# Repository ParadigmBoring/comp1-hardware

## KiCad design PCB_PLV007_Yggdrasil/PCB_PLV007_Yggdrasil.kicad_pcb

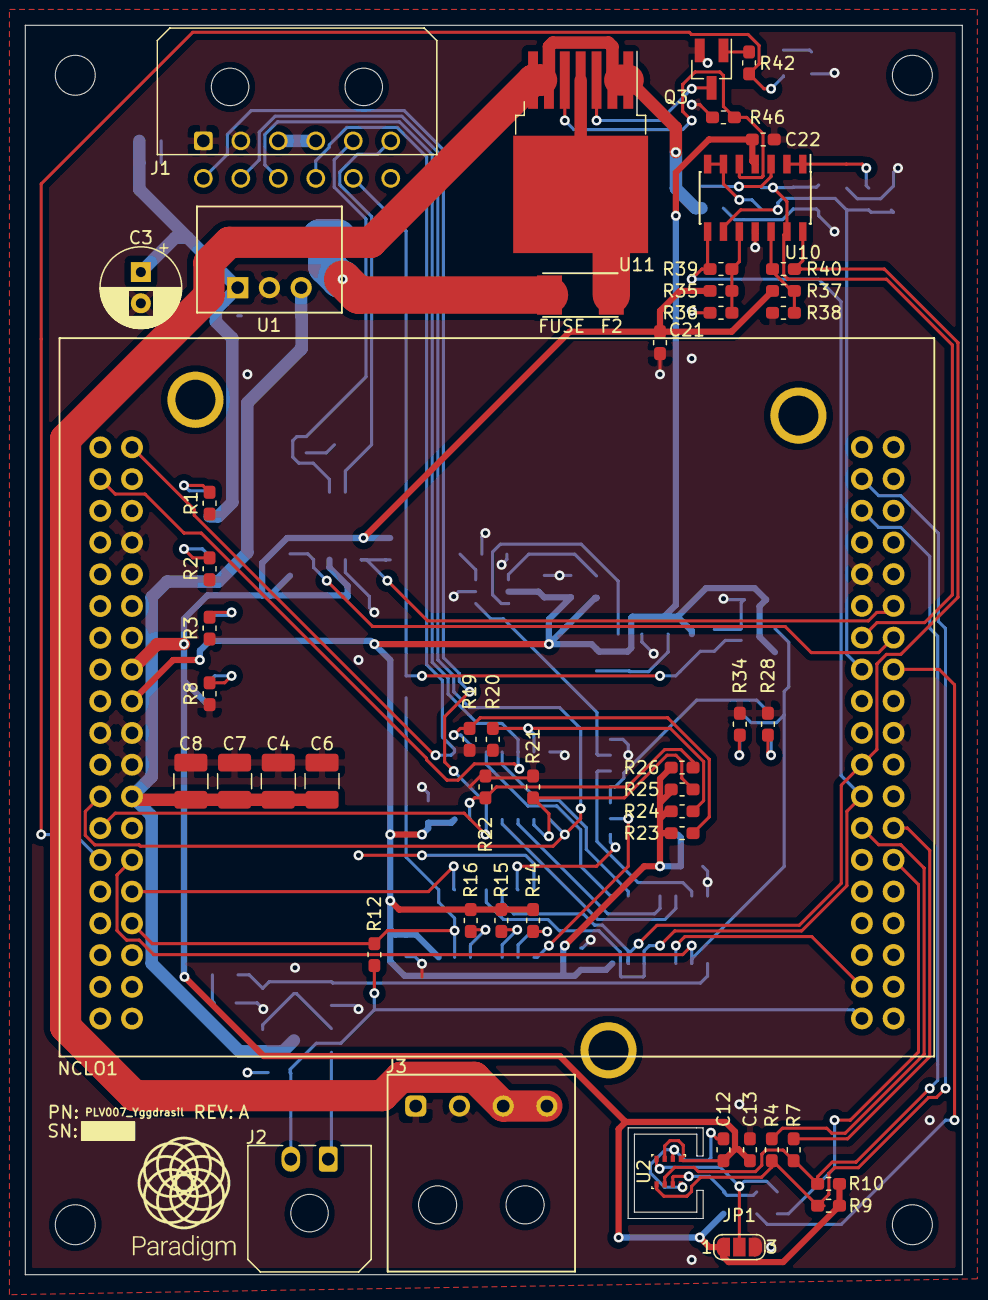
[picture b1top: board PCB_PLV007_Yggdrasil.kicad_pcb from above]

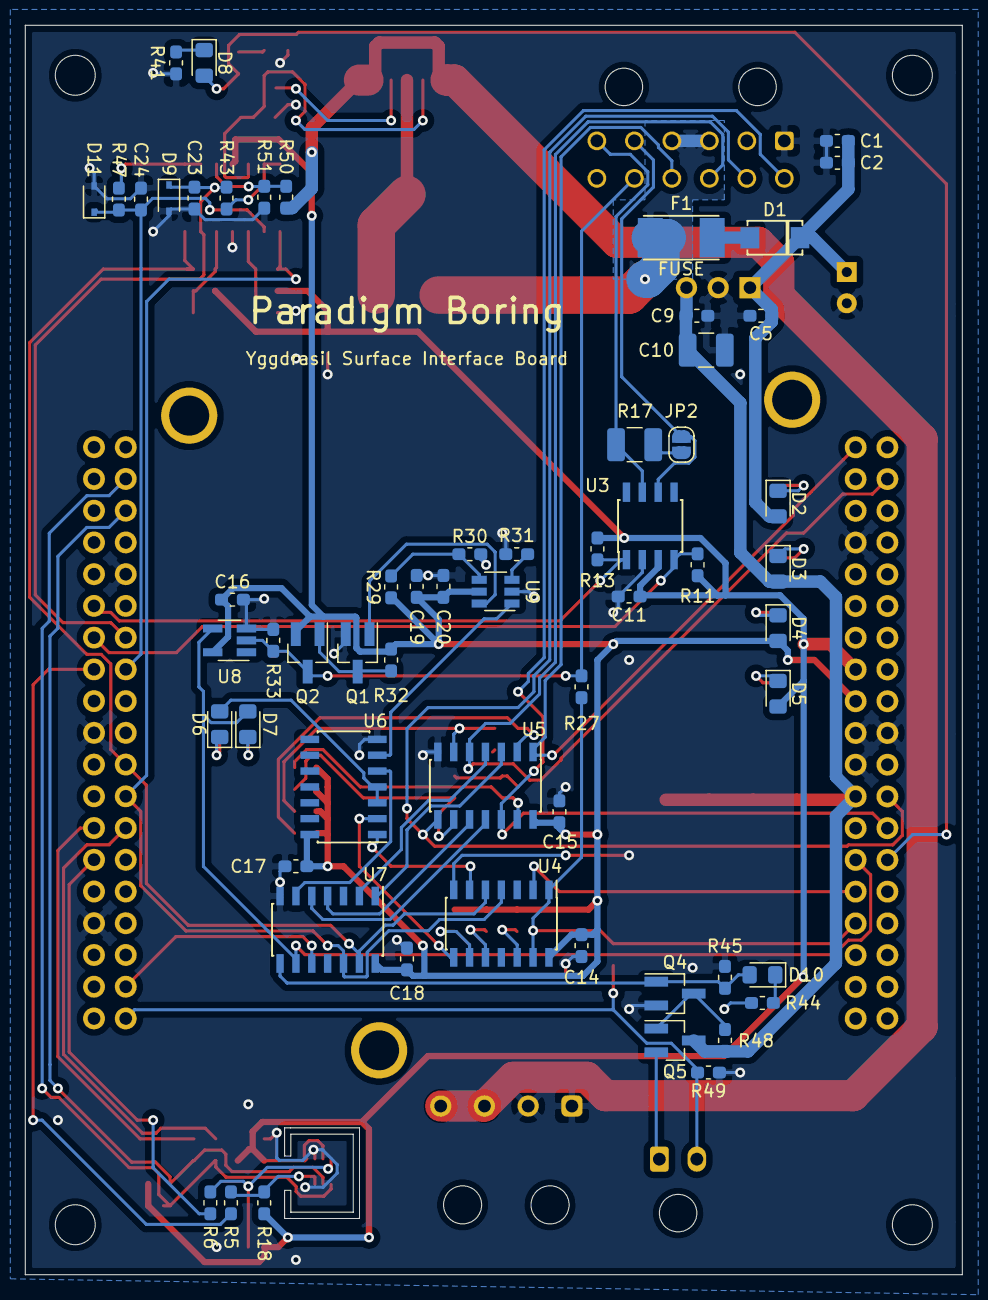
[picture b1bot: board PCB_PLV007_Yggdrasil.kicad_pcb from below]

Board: 2 copper layers, 75.0 x 100.0 mm, 110 parts (60 on the bottom side), 76 nets.

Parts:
C1, C2: DNP; C_0603_1608Metric_Pad1.05x0.95mm_HandSolder
C3: 47uF; CP_Radial_D6.3mm_P2.50mm
C4, C6, C7, C8, C10: 10uF; C_1210_3225Metric_Pad1.42x2.65mm_HandSolder
C5, C13, C20: 1uF; C_0603_1608Metric_Pad1.05x0.95mm_HandSolder
C9, C11, C12, C14, C15, C16, C17, C18, C19, C21, C22: 0.1uF; C_0603_1608Metric_Pad1.05x0.95mm_HandSolder
C23, C24: 0.47uF; C_0603_1608Metric_Pad1.05x0.95mm_HandSolder
D1: D_Schottky; DO-221AC
D2: 28V; LED_0805_2012Metric_Pad1.15x1.40mm_HandSolder
D3: 12V; LED_0805_2012Metric_Pad1.15x1.40mm_HandSolder
D4: 5V; LED_0805_2012Metric_Pad1.15x1.40mm_HandSolder
D5: 3V3; LED_0805_2012Metric_Pad1.15x1.40mm_HandSolder
D6: QB_IN; LED_0805_2012Metric_Pad1.15x1.40mm_HandSolder
D7: QB_OUT; LED_0805_2012Metric_Pad1.15x1.40mm_HandSolder
D8, D10: LED; LED_0805_2012Metric_Pad1.15x1.40mm_HandSolder
D9, D11: 3.3V; D_SOD-323
F1: 2A; BelFuse_0679H
F2: 15A; BelFuse_0679H
J1: Conn_01x12; Molex_Micro-Fit_3.0_43045-1200_2x06_P3.00mm_Horizontal
J2: UMBILICAL_MASTER; Molex_Micro-Fit_3.0_43650-0200_1x02_P3.00mm_Horizontal
J3: UMBILICAL_POWER; Molex_Ultra-Fit_172310-1204_1x04
JP1: BME280_ADDR; SolderJumper-3_P1.3mm_Open_RoundedPad1.0x1.5mm_NumberLabels
JP2: CAN_TERM; SolderJumper-2_P1.3mm_Open_RoundedPad1.0x1.5mm
NCLO1: NUCLEO-L476RG; ST_Nucleo-64
Q1, Q4: DMG2302UK-7; SOT-23_Handsoldering
Q2, Q5: DMP2123L-7; SOT-23_Handsoldering
Q3: MMBTA06LT1G; SOT-23_Handsoldering
R1: 11K; R_0603_1608Metric_Pad1.05x0.95mm_HandSolder
R2, R9, R10: 4.7K; R_0603_1608Metric_Pad1.05x0.95mm_HandSolder
R3: 1.5K; R_0603_1608Metric_Pad1.05x0.95mm_HandSolder
R4, R7, R14, R15, R16: 0; R_0603_1608Metric_Pad1.05x0.95mm_HandSolder
R5, R6, R11, R13, R19, R20, R21, R22, R23, R24, R25, R26: DNP; R_0603_1608Metric_Pad1.05x0.95mm_HandSolder
R8: 47; R_0603_1608Metric_Pad1.05x0.95mm_HandSolder
R12, R35, R37, R49, R51: 10K; R_0603_1608Metric_Pad1.05x0.95mm_HandSolder
R17: 120; R_1210_3225Metric_Pad1.42x2.65mm_HandSolder
R18: 0; C_0603_1608Metric_Pad1.05x0.95mm_HandSolder
R27, R32, R33: 47K; R_0603_1608Metric_Pad1.05x0.95mm_HandSolder
R28, R34, R41, R42, R43, R44, R47: 1K; R_0603_1608Metric_Pad1.05x0.95mm_HandSolder
R29: 1M; R_0603_1608Metric_Pad1.05x0.95mm_HandSolder
R30: 280K; R_0603_1608Metric_Pad1.05x0.95mm_HandSolder
R31: 604K; R_0603_1608Metric_Pad1.05x0.95mm_HandSolder
R36: 43K; R_0603_1608Metric_Pad1.05x0.95mm_HandSolder
R38: 16K; R_0603_1608Metric_Pad1.05x0.95mm_HandSolder
R39: 261K; R_0603_1608Metric_Pad1.05x0.95mm_HandSolder
R40: 95.3K; R_0603_1608Metric_Pad1.05x0.95mm_HandSolder
R45, R48, R50: 100K; R_0603_1608Metric_Pad1.05x0.95mm_HandSolder
R46: 2.1K; R_0603_1608Metric_Pad1.05x0.95mm_HandSolder
U1: R-78C12-1.0; Recom_R-78C-1.0
U2: BME280; Bosch_LGA-8_2.5x2.5mm_P0.65mm_ClockwisePinNumbering
U3: SN65HVD232; SOIC-8_3.9x4.9mm_P1.27mm
U4, U7: 74HC21; SOIC-14_3.9x8.7mm_P1.27mm
U5: 74HC266; SOIC-14_3.9x8.7mm_P1.27mm
U6: 74HC08; SOIC-14_3.9x8.7mm_P1.27mm
U8: 74LVC1G17; SOT-23-5_HandSoldering
U9: LTC6993xS6-1; TSOT-23-6
U10: LM2902; SOIC-14_3.9x8.7mm_P1.27mm
U11: BTS50055-1TMA; TO-263-7_TabPin4

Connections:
+3V3: C11.1, C12.1, C13.1, C21.1, D5.2, JP1.1, NCLO1.16, R9.1, R10.1, R11.1, R13.1, R18.1, R35.1, R37.1, U2.6, U2.8, U3.3
+5V: C14.1, C15.1, C16.1, C17.1, C18.1, C19.1, C20.1, C22.1, D4.2, NCLO1.18, Q2.2, R14.2, R15.2, R16.2, R23.1, R24.1, R25.1, R26.1, R29.1, R32.1, U4.14, U5.14, U6.14, U7.14, U8.5, U9.5, U10.4
+12V: C4.1, C6.1, C7.1, C8.1, C9.1, C10.1, D3.2, NCLO1.24, Q5.3, R48.1, U1.3
+28V: C1.1, C2.1, C3.1, C5.1, D1.1, D2.2, U1.1
/AvionicsHeartbeatTemplate/HEARTBEAT_INPUT_5: R14.1, U4.9
/AvionicsHeartbeatTemplate/HEARTBEAT_INPUT_6: R15.1, U4.10
/AvionicsHeartbeatTemplate/HEARTBEAT_INPUT_7: R16.1, U4.12
/BME280_CSB: R5.1, R18.2, U2.2
/BME280_SDO: JP1.2, R6.1, U2.5
/CANH: J1.6, R17.2, U3.7
/CANL: J1.5, JP2.2, U3.6
/CAN_RX: NCLO1.52, R11.2, U3.4
/CAN_TX: NCLO1.50, R13.2, U3.1
/C_SAFE: NCLO1.59, R40.1, U4.5, U7.13, U10.14
/C_SENSE: C23.1, D9.1, NCLO1.51, R43.2, U10.13
/HEARTBEAT: J1.11, Q2.3, R27.2, R33.1, U8.2
/HEARTBEAT_ADDRESS_1: J1.7, NCLO1.25, U5.12
/HEARTBEAT_ADDRESS_2: J1.8, NCLO1.23, U5.8
/HEARTBEAT_ADDRESS_3: J1.9, NCLO1.3, U5.5
/HEARTBEAT_ADDRESS_4: J1.10, NCLO1.2, U5.1
/HEARTBEAT_BUFF: D7.2, NCLO1.28, U7.9, U8.4
/HEARTBEAT_RESTART: NCLO1.32, R12.1, R27.1, U4.1, U4.13
/I2C_SCL: NCLO1.41, R4.1, R9.2, U2.4
/I2C_SDA: NCLO1.43, R7.1, R10.2, U2.3
/LOAD_SWITCH: D8.2, NCLO1.27, R42.2
/MCU_QB_INPUT: NCLO1.30, U4.2
/MCU_UHB_INPUT: NCLO1.73, U7.10
/UHB: J2.2, NCLO1.75, R12.2, R49.1
/UHBLS/UHB_MASTER: D10.2, Q4.1, R45.2, U7.8
/UHBLS/UMBILICAL_V+: J3.3, J3.4, R50.1, U11.1, U11.2, U11.6, U11.7
/VIN: F1.2, F2.2, J1.3, J1.4
/V_SAFE: NCLO1.61, R39.1, U4.4, U7.12, U10.8
/V_SENSE: C24.1, D11.1, NCLO1.53, R47.2, U10.9
GND: C1.2, C2.2, C3.2, C4.2, C5.2, C6.2, C7.2, C8.2, C9.2, C10.2, C11.2, C12.2, C13.2, C14.2, C15.2, C16.2, C17.2, C18.2, C19.2, C20.2, C21.2, C22.2, C23.2, C24.2, D9.2, D11.2, J1.1, J1.2, J3.1, J3.2, JP1.3, NCLO1.8, NCLO1.19, NCLO1.20, NCLO1.22, NCLO1.47, NCLO1.58, NCLO1.70, Q1.2, Q3.2, Q4.2, R1.2, R2.2, R3.2, R8.2, R19.1, R20.1, R21.1, R22.1, R28.2, R30.2, R31.2, R33.2, R34.2, R36.2, R38.2, R41.2, R44.2, R45.1, R46.2, R49.2, R51.2, U1.2, U2.1, U2.7, U3.2, U4.7, U5.7, U6.7, U7.7, U8.3, U9.2, U10.11
unnamed: D1.2, F1.1
unnamed: D2.1, R1.1
unnamed: D3.1, R2.1
unnamed: D4.1, R3.1
unnamed: D5.1, R8.1
unnamed: D6.1, R28.1
unnamed: D6.2, U6.3, U6.4
unnamed: D7.1, R34.1
unnamed: D8.1, R41.1
unnamed: D10.1, R44.1
unnamed: F2.1, U11.4
unnamed: J2.1, Q5.2
unnamed: JP2.1, R17.1
unnamed: NCLO1.54, R5.2
unnamed: NCLO1.63, R4.2
unnamed: NCLO1.64, R7.2
unnamed: NCLO1.66, R6.2
unnamed: Q1.1, U9.6
unnamed: Q1.3, Q2.1, R32.2
unnamed: Q3.1, R42.1
unnamed: Q3.3, U11.3
unnamed: Q4.3, Q5.1, R48.2
unnamed: R19.2, R23.2, U5.2
unnamed: R20.2, R24.2, U5.6
unnamed: R21.2, R25.2, U5.9
unnamed: R22.2, R26.2, U5.13
unnamed: R29.2, R30.1, U9.4
unnamed: R31.1, U9.3
unnamed: R35.2, R36.1, R39.2, U10.10
unnamed: R37.2, R38.1, R40.2, U10.12
unnamed: R43.1, U10.6, U10.7
unnamed: R46.1, U10.5, U11.5
unnamed: R47.1, U10.1, U10.2
unnamed: R50.2, R51.1, U10.3
unnamed: U4.6, U6.1
unnamed: U4.8, U6.2
unnamed: U5.3, U7.1
unnamed: U5.4, U7.2
unnamed: U5.10, U7.4
unnamed: U5.11, U7.5
unnamed: U6.5, U7.6
unnamed: U6.6, U9.1

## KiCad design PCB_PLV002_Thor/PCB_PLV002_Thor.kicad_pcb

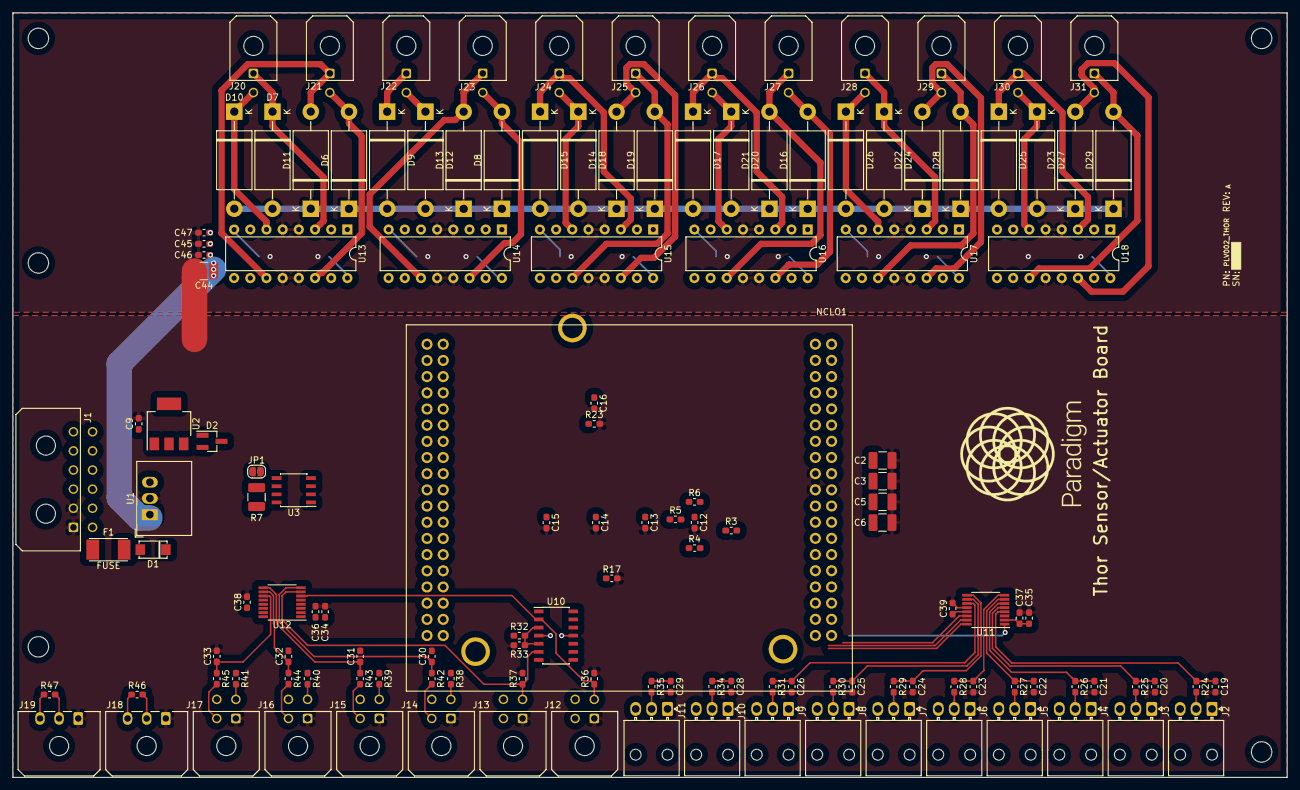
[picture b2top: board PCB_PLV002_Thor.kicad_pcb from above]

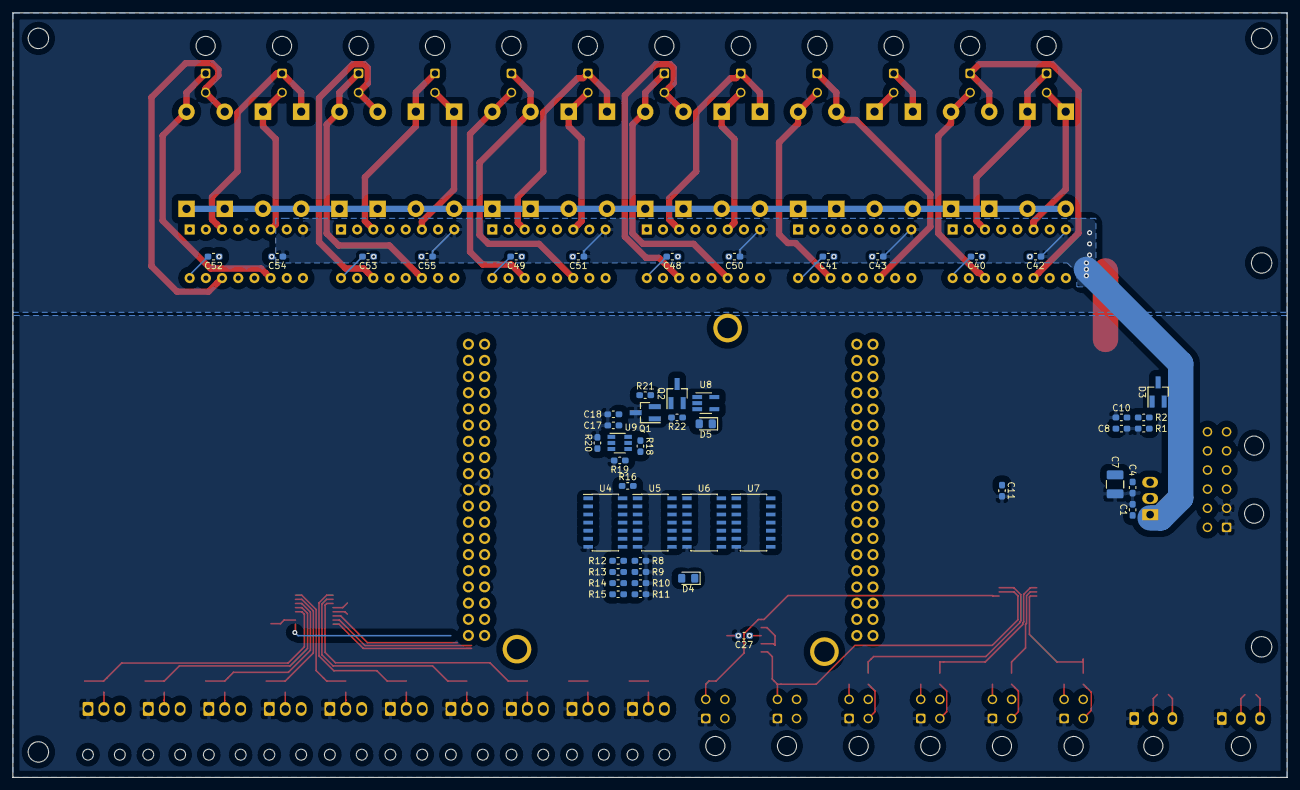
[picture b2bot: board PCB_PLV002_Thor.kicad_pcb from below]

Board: 2 copper layers, 200.0 x 120.0 mm, 185 parts (48 on the bottom side), 145 nets.

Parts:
C1, C10, C18, C34, C35, C42, C43, C45, C46, C50, C51, C54, C55: 1uF; C_0603_1608Metric_Pad1.05x0.95mm_HandSolder
C2, C3, C5, C6, C7, C44: 10uF; C_1210_3225Metric_Pad1.42x2.65mm_HandSolder
C4, C8, C9, C11, C12, C13, C14, C15, C16, C17, C19, C20, C21, C22, C23, C24, C25, C26, C27, C28, C29, C30, C31, C32, C33, C36, C37, C38, C39, C40, C41, C47, C48, C49, C52, C53: 0.1uF; C_0603_1608Metric_Pad1.05x0.95mm_HandSolder
D1: D_Schottky; DO-221AC
D2, D3: 1N4002; SOT-23_Handsoldering
D4: GREEN; LED_0805_2012Metric_Pad1.15x1.40mm_HandSolder
D5: BLUE; LED_0805_2012Metric_Pad1.15x1.40mm_HandSolder
D6, D7, D8, D9, D10, D11, D12, D13, D14, D15, D16, D17, D18, D19, D20, D21, D22, D23, D24, D25, D26, D27, D28, D29: 1.5KExxCA; D_DO-201AE_P15.24mm_Horizontal
F1: Fuse; BelFuse_0679H
J1: Conn_01x12; Molex_Micro-Fit_3.0_43045-1200_2x06_P3.00mm_Horizontal
J2: PRESS_1; Molex_Nano-Fit_105313-xx03_1x03_P2.50mm_Horizontal
J3: PRESS_2; Molex_Nano-Fit_105313-xx03_1x03_P2.50mm_Horizontal
J4: PRESS_3; Molex_Nano-Fit_105313-xx03_1x03_P2.50mm_Horizontal
J5: PRESS_4; Molex_Nano-Fit_105313-xx03_1x03_P2.50mm_Horizontal
J6: PRESS_5; Molex_Nano-Fit_105313-xx03_1x03_P2.50mm_Horizontal
J7: PRESS_6; Molex_Nano-Fit_105313-xx03_1x03_P2.50mm_Horizontal
J8: PRESS_7; Molex_Nano-Fit_105313-xx03_1x03_P2.50mm_Horizontal
J9: PRESS_8; Molex_Nano-Fit_105313-xx03_1x03_P2.50mm_Horizontal
J10: PRESS_9; Molex_Nano-Fit_105313-xx03_1x03_P2.50mm_Horizontal
J11: PRESS_10; Molex_Nano-Fit_105313-xx03_1x03_P2.50mm_Horizontal
J12: FLAMM_1; Molex_Micro-Fit_3.0_43045-0400_2x02_P3.00mm_Horizontal
J13: FLAMM_2; Molex_Micro-Fit_3.0_43045-0400_2x02_P3.00mm_Horizontal
J14: TEMPRESS_1; Molex_Micro-Fit_3.0_43045-0400_2x02_P3.00mm_Horizontal
J15: TEMPRESS_2; Molex_Micro-Fit_3.0_43045-0400_2x02_P3.00mm_Horizontal
J16: TEMPRESS_3; Molex_Micro-Fit_3.0_43045-0400_2x02_P3.00mm_Horizontal
J17: TEMPRESS_4; Molex_Micro-Fit_3.0_43045-0400_2x02_P3.00mm_Horizontal
J18: TACH_1; Molex_Micro-Fit_3.0_43650-0300_1x03_P3.00mm_Horizontal
J19: TACH_2; Molex_Micro-Fit_3.0_43650-0300_1x03_P3.00mm_Horizontal
J20, J21, J22, J23, J24, J25, J26, J27, J28, J29, J30, J31: Conn_01x02; Molex_Micro-Fit_3.0_43045-0200_2x01_P3.00mm_Horizontal
JP1: CAN_TERM; SolderJumper-2_P1.3mm_Open_RoundedPad1.0x1.5mm
NCLO1: NUCLEO-L476RG; ST_Nucleo-64
Q1: DMG2302UK-7; SOT-23_Handsoldering
Q2: DMP2123L-7; SOT-23_Handsoldering
R1: 1.1K; R_0603_1608Metric_Pad1.05x0.95mm_HandSolder
R2: 240; R_0603_1608Metric_Pad1.05x0.95mm_HandSolder
R3, R4, R5, R6: 0; R_0603_1608Metric_Pad1.05x0.95mm_HandSolder
R7: 120; R_1210_3225Metric_Pad1.42x2.65mm_HandSolder
R8, R9, R10, R11, R12, R13, R14, R15: DNP; R_0603_1608Metric_Pad1.05x0.95mm_HandSolder
R16, R21, R22: 47K; R_0603_1608Metric_Pad1.05x0.95mm_HandSolder
R17, R23, R24, R25, R26, R27, R28, R29, R30, R31, R34, R35, R42, R43, R44, R45: 1K; R_0603_1608Metric_Pad1.05x0.95mm_HandSolder
R18: 1M; R_0603_1608Metric_Pad1.05x0.95mm_HandSolder
R19: 280K; R_0603_1608Metric_Pad1.05x0.95mm_HandSolder
R20: 604K; R_0603_1608Metric_Pad1.05x0.95mm_HandSolder
R32, R36, R37, R38, R39, R40, R41, R46, R47: 10K; R_0603_1608Metric_Pad1.05x0.95mm_HandSolder
R33: 22K; R_0603_1608Metric_Pad1.05x0.95mm_HandSolder
U1: R-78B12-2.0; Converter_DCDC_RECOM_R-78B-2.0_THT
U2: LM317DCYRG3; SOT-223-3_TabPin2
U3: SN65HVD232; SOIC-8_3.9x4.9mm_P1.27mm
U4, U7: 74HC21; SOIC-14_3.9x8.7mm_P1.27mm
U5: 74HC266; SOIC-14_3.9x8.7mm_P1.27mm
U6: 74HC08; SOIC-14_3.9x8.7mm_P1.27mm
U8: 74LVC1G17; SOT-23-5_HandSoldering
U9: LTC6993xS6-1; TSOT-23-6
U10: LM2902; SOIC-14_3.9x8.7mm_P1.27mm
U11, U12: ADC128S022; TSSOP-16_4.4x5mm_P0.65mm
U13, U14, U15, U16, U17, U18: L293D; DIP-16_W7.62mm

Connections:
7V: C10.1, D2.2, D3.1, J12.2, J13.2, R2.1, U2.2
+3V3: C11.1, C38.1, C39.1, NCLO1.16, R38.1, R39.1, R40.1, R41.1, U3.3, U11.13, U12.13
+5V: C12.1, C13.1, C14.1, C15.1, C16.1, C17.1, C18.1, C27.1, C34.1, C35.1, C36.1, C37.1, C40.2, C41.2, C48.2, C49.2, C52.2, C53.2, J12.4, J13.4, J18.3, J19.3, NCLO1.18, Q2.3, R3.2, R4.2, R5.2, R6.2, R12.1, R13.1, R14.1, R15.1, R18.1, R21.1, R32.1, R46.1, R47.1, U4.14, U5.14, U6.14, U7.14, U8.5, U9.5, U10.4, U11.2, U12.2, U13.16, U14.16, U15.16, U16.16, U17.16, U18.16
+12V: C2.1, C3.1, C4.1, C5.1, C6.1, C7.1, C8.1, D2.1, NCLO1.24, U1.3, U2.3
+24V: C1.1, C42.1, C43.1, C44.1, C45.1, C46.1, C47.1, C50.1, C51.1, C54.1, C55.1, D1.1, J2.3, J3.3, J4.3, J5.3, J6.3, J7.3, J8.3, J9.3, J10.3, J11.3, J14.4, J15.4, J16.4, J17.4, U1.1, U13.8, U14.8, U15.8, U16.8, U17.8, U18.8
/ACT_EN_1: NCLO1.49, U13.1, U13.9
/ACT_EN_2: NCLO1.32, U14.1, U14.9
/ACT_EN_3: NCLO1.75, U15.1, U15.9
/ACT_EN_4: NCLO1.73, U16.1
/ACT_EN_5: NCLO1.71, U16.9
/ACT_EN_6: NCLO1.59, U18.1, U18.9
/ACT_EN_7: NCLO1.61, U17.1
/ACT_EN_8: NCLO1.15, U17.9
/ACT_IN_1: NCLO1.27, U13.2
/ACT_IN_2: NCLO1.25, U13.7
/ACT_IN_3: NCLO1.23, U13.10
/ACT_IN_4: NCLO1.3, U13.15
/ACT_IN_5: NCLO1.2, U14.2
/ACT_IN_6: NCLO1.1, U14.7
/ACT_IN_7: NCLO1.39, U14.10
/ACT_IN_8: NCLO1.40, U14.15
/ACT_IN_9: NCLO1.57, U15.2
/ACT_IN_10: NCLO1.42, U15.7
/ACT_IN_11: NCLO1.44, U15.10
/ACT_IN_12: NCLO1.72, U15.15
/ACT_IN_13: NCLO1.37, U16.2
/ACT_IN_14: NCLO1.35, U16.7
/ACT_IN_15: NCLO1.36, U16.10
/ACT_IN_16: NCLO1.38, U16.15
/ACT_IN_17: NCLO1.69, U18.2
/ACT_IN_18: NCLO1.65, U18.7
/ACT_IN_19: NCLO1.67, U18.10
/ACT_IN_20: NCLO1.55, U18.15
/ACT_IN_21: NCLO1.21, U17.2
/ACT_IN_22: NCLO1.41, U17.7
/ACT_IN_23: NCLO1.43, U17.10
/ACT_IN_24: NCLO1.63, U17.15
/ADC1_nCS: NCLO1.56, U11.1
/ADC2_nCS: NCLO1.54, U12.1
/Acquisition/FLAMM_1: J12.3, R36.1, U10.2, U12.6
/Acquisition/FLAMM_2: J13.3, R37.1, U10.6, U12.7
/Acquisition/FLAMM_THRESH: R32.2, R33.1, U10.3, U10.5
/Acquisition/PRESS_1: C19.1, R24.1, U11.4
/Acquisition/PRESS_2: C20.1, R25.1, U11.5
/Acquisition/PRESS_3: C21.1, R26.1, U11.6
/Acquisition/PRESS_4: C22.1, R27.1, U11.7
/Acquisition/PRESS_5: C23.1, R28.1, U11.8
/Acquisition/PRESS_6: C24.1, R29.1, U11.9
/Acquisition/PRESS_7: C25.1, R30.1, U11.10
/Acquisition/PRESS_8: C26.1, R31.1, U11.11
/Acquisition/PRESS_9: C28.1, R34.1, U12.4
/Acquisition/PRESS_10: C29.1, R35.1, U12.5
/Acquisition/TPRESS_1: C30.1, R42.1, U12.8
/Acquisition/TPRESS_2: C31.1, R43.1, U12.9
/Acquisition/TPRESS_3: C32.1, R44.1, U12.10
/Acquisition/TPRESS_4: C33.1, R45.1, U12.11
/AvionicsHeartbeatTemplate/HEARTBEAT_INPUT_4: R3.1, U4.5
/AvionicsHeartbeatTemplate/HEARTBEAT_INPUT_5: R4.1, U4.9
/AvionicsHeartbeatTemplate/HEARTBEAT_INPUT_6: R5.1, U4.10
/AvionicsHeartbeatTemplate/HEARTBEAT_INPUT_7: R6.1, U4.12
/CANH: J1.6, R7.2, U3.7
/CANL: J1.5, JP1.2, U3.6
/CAN_RX: NCLO1.52, U3.4
/CAN_TX: NCLO1.50, U3.1
/FLAMM_SAFE_1: U4.2, U10.1
/FLAMM_SAFE_2: U4.4, U10.7
/HEARTBEAT: J1.11, Q2.2, R16.2, R22.1, U8.2
/HEARTBEAT_ADDRESS_1: J1.7, U5.12
/HEARTBEAT_ADDRESS_2: J1.8, U5.8
/HEARTBEAT_ADDRESS_3: J1.9, U5.5
/HEARTBEAT_ADDRESS_4: J1.10, U5.1
/HEARTBEAT_BUFF: D5.2, NCLO1.13, U8.4
/HEARTBEAT_RESTART: NCLO1.60, R16.1, U4.13
/MCU_QB_INPUT: NCLO1.62, U4.1
/SPI_MISO: NCLO1.66, U11.14, U12.14
/SPI_MOSI: NCLO1.64, U11.15, U12.15
/SPI_SCLK: NCLO1.68, U11.16, U12.16
/TACH_1: J18.2, R46.2
/TACH_2: J19.2, R47.2
/TEMP_1: J14.3, NCLO1.28, R38.2
/TEMP_2: J15.3, NCLO1.30, R39.2
/TEMP_3: J16.3, NCLO1.51, R40.2
/TEMP_4: J17.3, NCLO1.53, R41.2
/VIN: F1.2, J1.3, J1.4
GND: C1.2, C2.2, C3.2, C4.2, C5.2, C6.2, C7.2, C8.2, C9.2, C10.2, C11.2, C12.2, C13.2, C14.2, C15.2, C16.2, C17.2, C18.2, C19.2, C20.2, C21.2, C22.2, C23.2, C24.2, C25.2, C26.2, C27.2, C28.2, C29.2, C30.2, C31.2, C32.2, C33.2, C34.2, C35.2, C36.2, C37.2, C38.2, C39.2, C40.1, C41.1, C42.2, C43.2, C44.2, C45.2, C46.2, C47.2, C48.1, C49.1, C50.2, C51.2, C52.1, C53.1, C54.2, C55.2, D6.1, D7.2, D8.1, D9.2, D10.2, D11.1, D12.2, D13.1, D14.1, D15.2, D16.1, D17.2, D18.2, D19.1, D20.2, D21.1, D22.1, D23.1, D24.2, D25.2, D26.2, D27.2, D28.1, D29.1, J1.1, J1.2, J2.1, J3.1, J4.1, J5.1, J6.1, J7.1, J8.1, J9.1, J10.1, J11.1, J12.1, J13.1, J14.1, J15.1, J16.1, J17.1, J18.1, J19.1, NCLO1.8, NCLO1.19, NCLO1.20, NCLO1.22, NCLO1.47, NCLO1.58, NCLO1.70, Q1.3, R1.2, R8.1, R9.1, R10.1, R11.1, R17.2, R19.2, R20.2, R22.2, R23.2, R33.2, R36.2, R37.2, U1.2, U3.2, U4.7, U5.7, U6.7, U7.7, U8.3, U9.2, U10.11, U11.3, U11.12, U12.3, U12.12, U13.4, U13.5, U13.12, U13.13, U14.4, U14.5, U14.12, U14.13, U15.4, U15.5, U15.12, U15.13, U16.4, U16.5, U16.12, U16.13, U17.4, U17.5, U17.12, U17.13, U18.4, U18.5, U18.12, U18.13
unnamed: C9.1, D3.2, R1.1, R2.2, U2.1
unnamed: D1.2, F1.1
unnamed: D4.1, R17.1
unnamed: D4.2, U6.3, U6.4
unnamed: D5.1, R23.1
unnamed: D6.2, J21.2, U13.14
unnamed: D7.1, J20.1, U13.3
unnamed: D8.2, J23.2, U14.14
unnamed: D9.1, J22.1, U14.3
unnamed: D10.1, J20.2, U13.6
unnamed: D11.2, J21.1, U13.11
unnamed: D12.1, J22.2, U14.6
unnamed: D13.2, J23.1, U14.11
unnamed: D14.2, J25.2, U15.14
unnamed: D15.1, J24.1, U15.3
unnamed: D16.2, J27.2, U16.14
unnamed: D17.1, J26.1, U16.3
unnamed: D18.1, J24.2, U15.6
unnamed: D19.2, J25.1, U15.11
unnamed: D20.1, J26.2, U16.6
unnamed: D21.2, J27.1, U16.11
unnamed: D22.2, J29.2, U17.14
unnamed: D23.2, J31.2, U18.14
unnamed: D24.1, J28.1, U17.3
unnamed: D25.1, J30.1, U18.3
unnamed: D26.1, J28.2, U17.6
unnamed: D27.1, J30.2, U18.6
unnamed: D28.2, J29.1, U17.11
unnamed: D29.2, J31.1, U18.11
unnamed: J2.2, R24.2
unnamed: J3.2, R25.2
unnamed: J4.2, R26.2
unnamed: J5.2, R27.2
unnamed: J6.2, R28.2
unnamed: J7.2, R29.2
unnamed: J8.2, R30.2
unnamed: J9.2, R31.2
unnamed: J10.2, R34.2
unnamed: J11.2, R35.2
unnamed: J14.2, R42.2
unnamed: J15.2, R43.2
unnamed: J16.2, R44.2
unnamed: J17.2, R45.2
unnamed: JP1.1, R7.1
unnamed: Q1.1, U9.6
unnamed: Q1.2, Q2.1, R21.2
unnamed: R10.2, R14.2, U5.9
unnamed: R11.2, R15.2, U5.13
unnamed: R8.2, R12.2, U5.2
unnamed: R9.2, R13.2, U5.6
unnamed: R18.2, R19.1, U9.4
unnamed: R20.1, U9.3
unnamed: U4.6, U6.1
unnamed: U4.8, U6.2
unnamed: U5.3, U7.1
unnamed: U5.4, U7.2
unnamed: U5.10, U7.4
unnamed: U5.11, U7.5
unnamed: U6.5, U7.6
unnamed: U6.6, U9.1

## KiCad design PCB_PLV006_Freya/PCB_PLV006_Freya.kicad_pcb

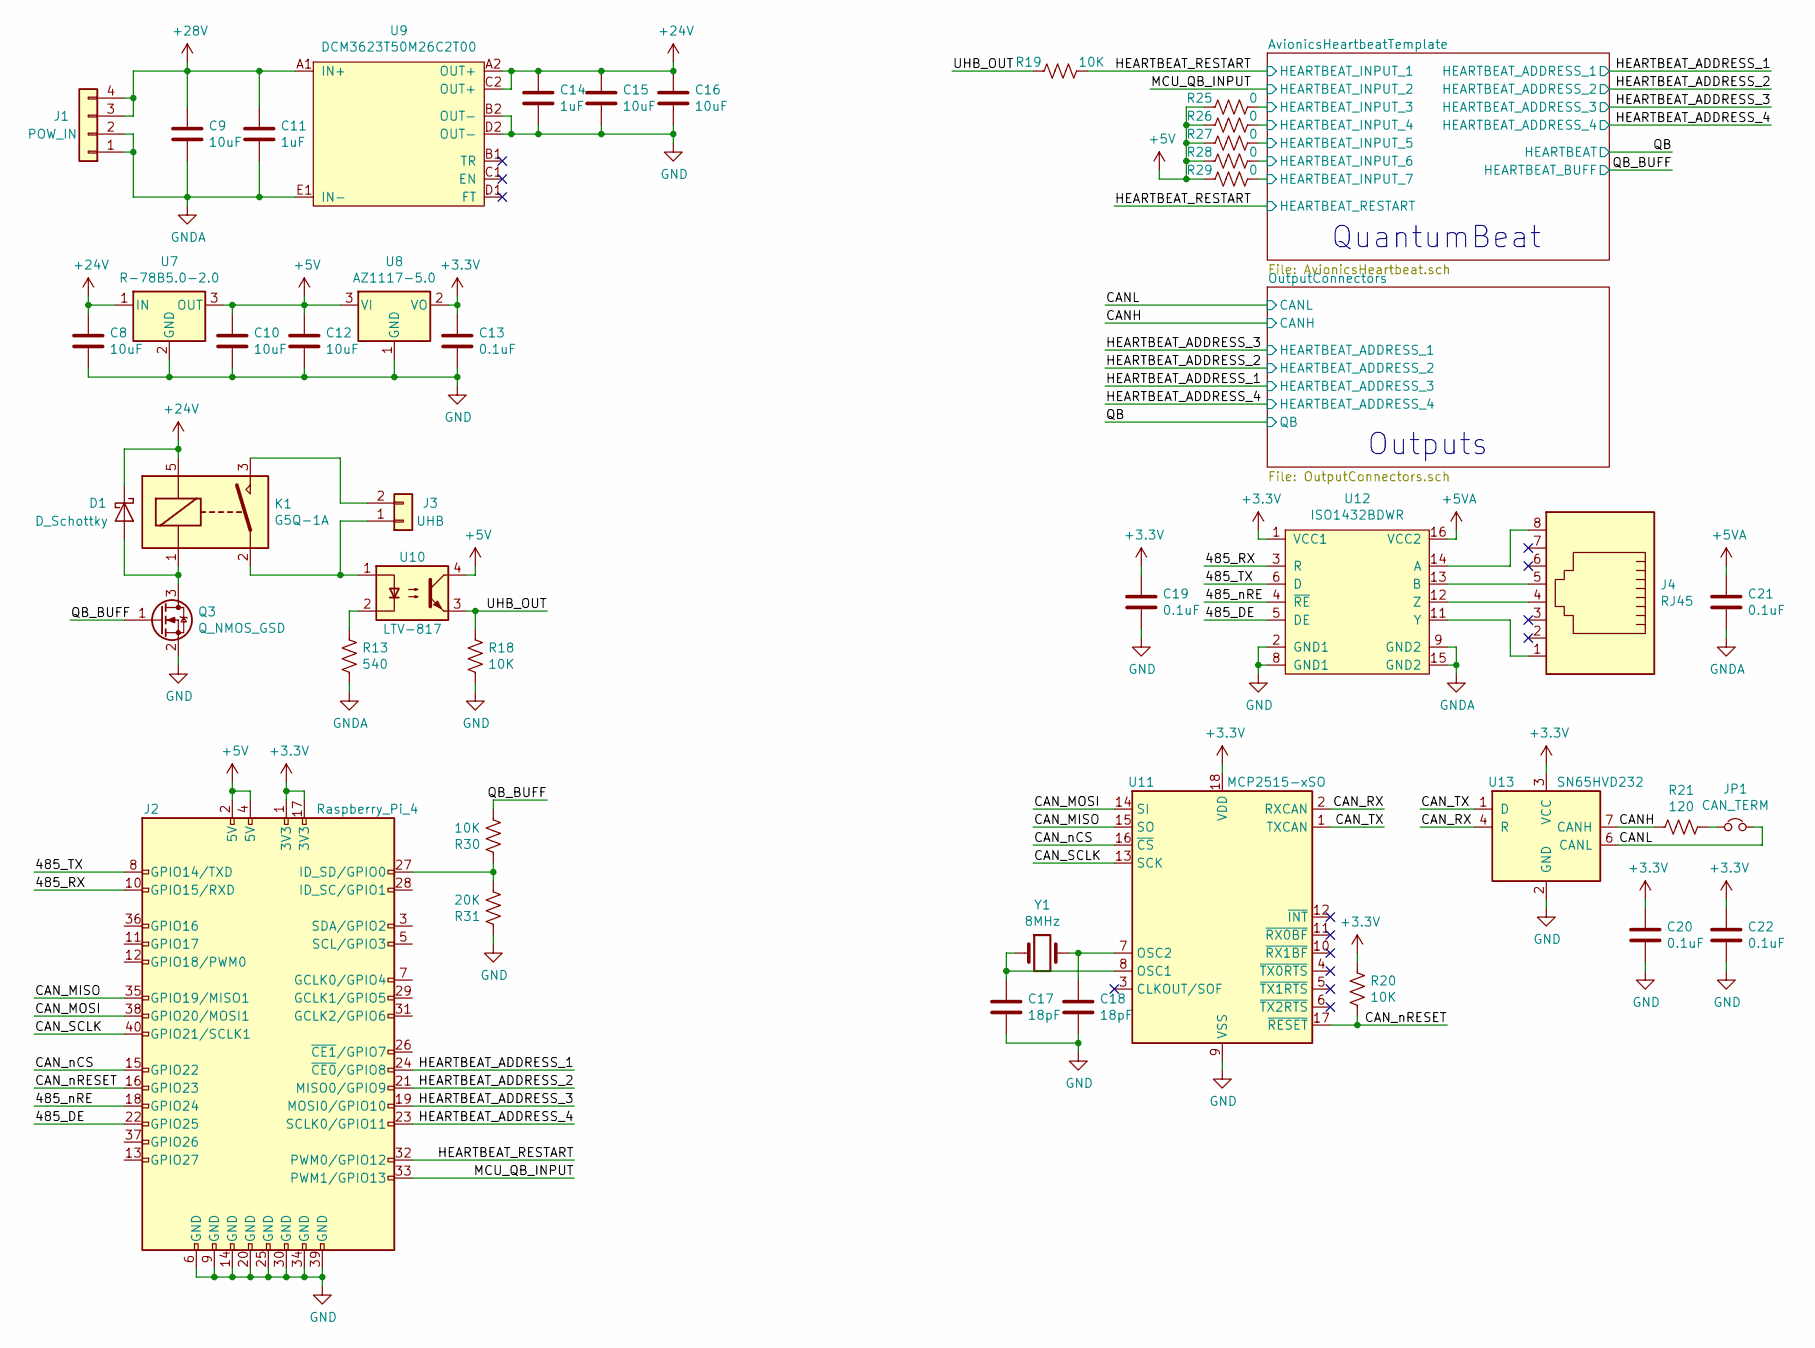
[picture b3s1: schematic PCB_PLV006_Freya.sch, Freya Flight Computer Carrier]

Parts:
C8, C9, C10, C12, C15, C16: 10uF; C_1210_3225Metric_Pad1.42x2.65mm_HandSolder
C11, C14: 1uF; C_0603_1608Metric_Pad1.05x0.95mm_HandSolder
C13, C19, C20, C21, C22: 0.1uF; C_0603_1608Metric_Pad1.05x0.95mm_HandSolder
C17, C18: 18pF; C_0603_1608Metric_Pad1.05x0.95mm_HandSolder
D1: D_Schottky; DO-221AC
J1: POW_IN; Molex_Ultra-Fit_172310-1204_1x04
J2: Raspberry_Pi_4; RPI4
J3: UHB; Molex_Micro-Fit_3.0_43045-0400_2x02_P3.00mm_Horizontal
J4: RJ45; RJ45_Amphenol_RJHSE538X
JP1: CAN_TERM; SolderJumper-2_P1.3mm_Open_RoundedPad1.0x1.5mm
K1: G5Q-1A; Relay_SPST_Omron-G5Q-1A
Q3: Q_NMOS_GSD; SOT-23_Handsoldering
R13: 540; R_0603_1608Metric_Pad1.05x0.95mm_HandSolder
R18, R19, R20, R30: 10K; R_0603_1608Metric_Pad1.05x0.95mm_HandSolder
R21: 120; R_1210_3225Metric_Pad1.42x2.65mm_HandSolder
R25, R26, R27, R28, R29: 0; R_0603_1608Metric_Pad1.05x0.95mm_HandSolder
R31: 20K; R_0603_1608Metric_Pad1.05x0.95mm_HandSolder
U7: R-78B5.0-2.0; Converter_DCDC_RECOM_R-78B-2.0_THT
U8: AZ1117-5.0; SOT-223-3_TabPin2
U9: DCM3623T50M26C2T00; Vicor_DCM
U10: LTV-817; DIP-4_W7.62mm
U11: MCP2515-xSO; SOIC-18W_7.5x11.6mm_P1.27mm
U12: ISO1432BDWR; SOIC-16W_7.5x10.3mm_P1.27mm
U13: SN65HVD232; SOIC-8_3.9x4.9mm_P1.27mm
Y1: 8MHz; Crystal_SMD_HC49-SD

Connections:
+3V3: C13.1, C19.1, C20.1, C22.1, J2.1 (3V3), J2.17 (3V3), R20.1, U8.2 (VO), U11.18 (VDD), U12.1 (VCC1), U13.3 (VCC)
+5V: C10.1, C12.1, J2.2 (5V), J2.4 (5V), R25.1, R26.1, R27.1, R28.1, R29.1, U7.3 (OUT), U8.3 (VI), U10.4; also elsewhere on the board
+5VA: C21.1, U12.16 (VCC2)
+24V: C8.1, C14.1, C15.1, C16.1, D1.1 (K), K1.5, U7.1 (IN), U9.A2 (OUT+), U9.C2 (OUT+); also elsewhere on the board
+28V: C9.1, C11.1, J1.3, J1.4, U9.A1 (IN+)
/485_DE: J2.22 (GPIO25), U12.5 (DE)
/485_RX: J2.10 (GPIO15/RXD), U12.3 (R)
/485_TX: J2.8 (GPIO14/TXD), U12.6 (D)
/485_nRE: J2.18 (GPIO24), U12.4 (~RE~)
/AvionicsHeartbeatTemplate/HEARTBEAT_INPUT_3: R25.2; also elsewhere on the board
/AvionicsHeartbeatTemplate/HEARTBEAT_INPUT_4: R26.2; also elsewhere on the board
/AvionicsHeartbeatTemplate/HEARTBEAT_INPUT_5: R27.2; also elsewhere on the board
/AvionicsHeartbeatTemplate/HEARTBEAT_INPUT_6: R28.2; also elsewhere on the board
/AvionicsHeartbeatTemplate/HEARTBEAT_INPUT_7: R29.2; also elsewhere on the board
/CANH: R21.2, U13.7 (CANH); also elsewhere on the board
/CANL: JP1.2, U13.6 (CANL); also elsewhere on the board
/CAN_MISO: J2.35 (GPIO19/MISO1), U11.15 (SO)
/CAN_MOSI: J2.38 (GPIO20/MOSI1), U11.14 (SI)
/CAN_RX: U11.2 (RXCAN), U13.4 (R)
/CAN_SCLK: J2.40 (GPIO21/SCLK1), U11.13 (SCK)
/CAN_TX: U11.1 (TXCAN), U13.1 (D)
/CAN_nCS: J2.15 (GPIO22), U11.16 (~CS)
/CAN_nRESET: J2.16 (GPIO23), R20.2, U11.17 (~RESET)
/HEARTBEAT_ADDRESS_1: J2.24 (~CE0~/GPIO8); also elsewhere on the board
/HEARTBEAT_ADDRESS_2: J2.21 (MISO0/GPIO9); also elsewhere on the board
/HEARTBEAT_ADDRESS_3: J2.19 (MOSI0/GPIO10); also elsewhere on the board
/HEARTBEAT_ADDRESS_4: J2.23 (SCLK0/GPIO11); also elsewhere on the board
/HEARTBEAT_RESTART: J2.32 (PWM0/GPIO12), R19.2; also elsewhere on the board
/MCU_QB_INPUT: J2.33 (PWM1/GPIO13); also elsewhere on the board
/QB_BUFF: Q3.1 (G), R30.2; also elsewhere on the board
/UHB_OUT: R18.1, R19.1, U10.3
GND: C8.2, C10.2, C12.2, C13.2, C14.2, C15.2, C16.2, C17.2, C18.2, C19.2, C20.2, C22.2, J2.6 (GND), J2.9 (GND), J2.14 (GND), J2.20 (GND), J2.25 (GND), J2.30 (GND), J2.34 (GND), J2.39 (GND), Q3.2 (S), R18.2, R31.1, U7.2 (GND), U8.1 (GND), U9.B2 (OUT-), U9.D2 (OUT-), U11.9 (VSS), U12.2 (GND1), U12.8 (GND1), U13.2 (GND); also elsewhere on the board
GNDA: C9.2, C11.2, C21.2, J1.1, J1.2, R13.2, U9.E1 (IN-), U12.9 (GND2), U12.15 (GND2)
unnamed: C17.1, U11.8 (OSC1), Y1.1
unnamed: C18.1, U11.7 (OSC2), Y1.2
unnamed: D1.2 (A), K1.1, Q3.3 (D)
unnamed: J2.27 (ID_SD/GPIO0), R30.1, R31.2
unnamed: J3.1, K1.2, U10.1
unnamed: J3.2, K1.3
unnamed: J4.1, U12.11 (Y)
unnamed: J4.4, U12.12 (Z)
unnamed: J4.5, U12.13 (B)
unnamed: J4.8, U12.14 (A)
unnamed: JP1.1, R21.1
unnamed: R13.1, U10.2

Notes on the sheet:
QuantumBeat
Outputs
